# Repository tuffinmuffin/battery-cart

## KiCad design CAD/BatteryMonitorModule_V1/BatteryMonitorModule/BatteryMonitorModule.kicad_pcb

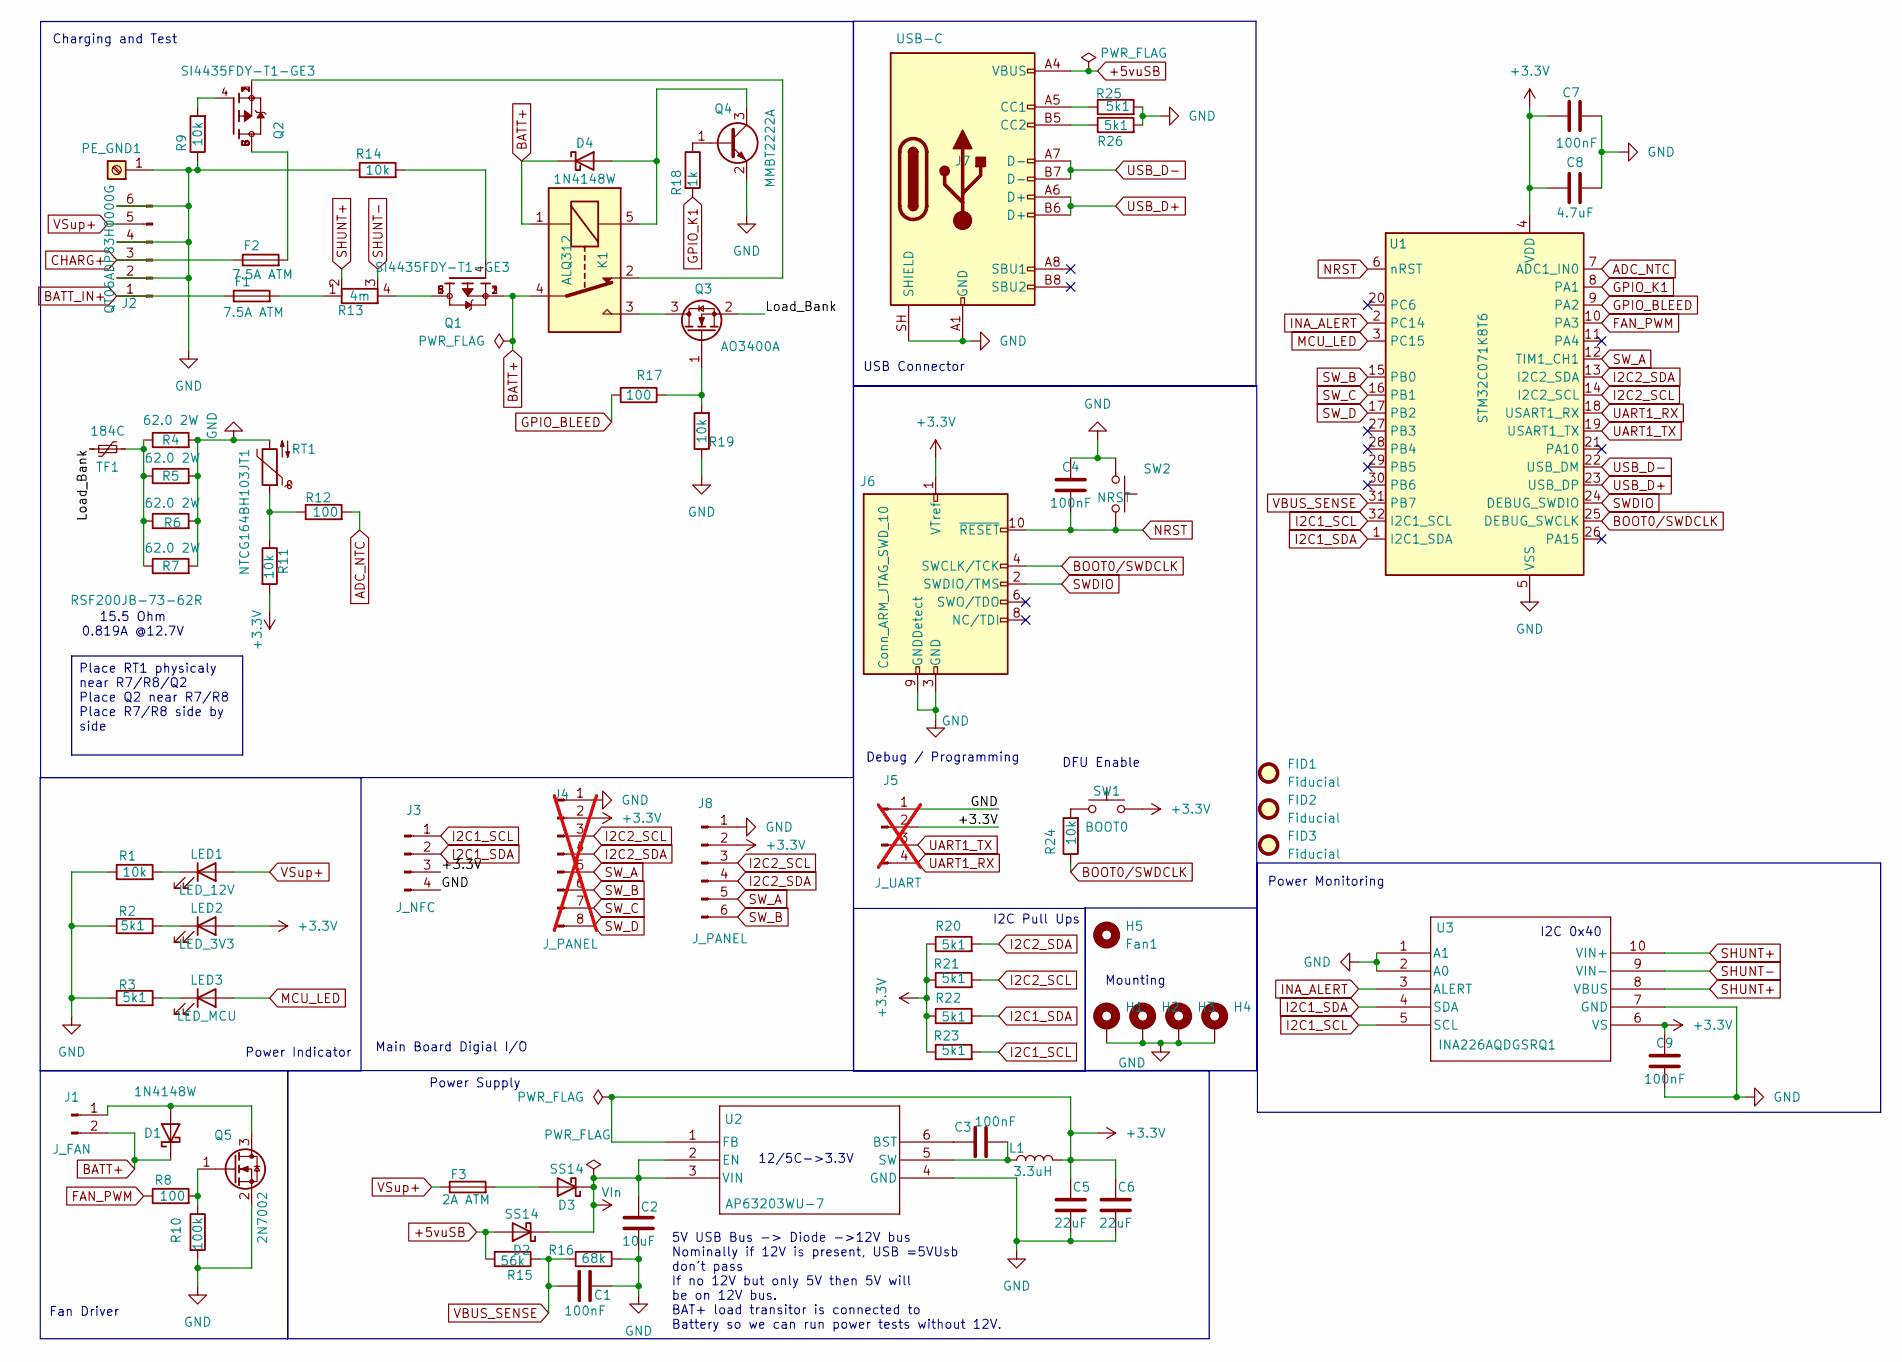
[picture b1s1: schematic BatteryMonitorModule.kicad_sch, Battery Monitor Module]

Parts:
C1, C3, C4, C7, C9: 100nF; C_0402_1005Metric; MPN CL05B104KO5NNNC; Digikey PN 1276-1001-6-ND
C2: 10uF; C_0805_2012Metric; MPN CL21A106KAYNNNG; Digikey PN 1276-6454-6-ND
C5, C6: 22uF; C_0805_2012Metric; MPN CL21A226MQQNNNE; Digikey PN 1276-1100-6-ND
C8: 4.7uF; C_0603_1608Metric; MPN CL10A475KP8NNNC; Digikey PN 1276-1044-6-ND
D1, D4: 1N4148W; D_SOD-123; MPN 1N4148W; Digikey PN 5399-1N4148WDKR-ND
D2, D3: SS14; D_SOD-123; MPN SS14; Digikey PN 5399-SS14DKR-ND
F1, F2: 7.5A ATM; FUSE_BK-6013; MPN BK-6013; Digikey PN BK-6013-ND
F3: 2A ATM; FUSE_BK-6013; MPN BK-6013; Digikey PN BK-6013-ND
FID1, FID2, FID3: Fiducial; Fiducial_0.5mm_Mask1.5mm
H1, H2, H3, H4: MountingHole_Pad; MountingHole_3.2mm_M3_DIN965_Pad
H5: Fan1; 2510FanOverhead
J1: J_FAN; PinHeader_1x02_P2.54mm_Vertical; MPN B2B-XH-A; Digikey PN 455-B2B-XH-A-ND
J2: QT06ADP83H0000G; MPN QT06ADP83H0000G; Digikey PN 1818-QT06ADP83H0000G-ND
J3: J_NFC; JST_XH_B4B-XH-A_1x04_P2.50mm_Vertical; MPN B4B-XH-A; Digikey PN 455-B4B-XH-A-ND
J4: J_PANEL; JST_XH_B8B-XH-AM_1x08_P2.50mm_Vertical; not fitted
J5: J_UART; PinHeader_1x04_P2.54mm_Vertical; not fitted
J6: Conn_ARM_JTAG_SWD_10; PinHeader_2x05_P1.27mm_Vertical; MPN Generic; Digikey PN N/A
J7: USB-C; SAMESKY_UJ20-C-H-G-SMT-1-P16-TR; PARTREV A4; Digikey PN 2223-UJ20-C-H-G-SMT-1-P16-TRDKR-ND
J8: J_PANEL; PinHeader_2x03_P2.54mm_Vertical
K1: ALQ312; Relay_SPDT_Omron-G5Q-1; MPN ALQ312
L1: 3.3uH; IND_BOURNS_SRR4028; MPN SRR4028-3R3Y; Digikey PN SRR4028-3R3YTR-ND
LED1: LED_12V; LED_0603_1608Metric; MPN LTST-C190KGKT; Digikey PN 160-1435-6-ND
LED2: LED_3V3; LED_0603_1608Metric; MPN LTST-C190KGKT; Digikey PN 160-1435-6-ND
LED3: LED_MCU; LED_0603_1608Metric; MPN LTST-C190KGKT; Digikey PN 160-1435-6-ND
PE_GND1: Keystone 4966; KEYSTONE_4966; MPN 4966; Digikey PN 36-4966-ND
Q1, Q2: SI4435FDY-T1-GE3; SOIC-8_3.9x4.9mm_P1.27mm; PARTREV I; Digikey PN SI4435FDY-T1-GE3DKR-ND
Q3: AO3400A; SOT-23; MPN AO3400A; Digikey PN 785-1000-2-ND
Q4: MMBT2222A; SOT-23; MPN MMBT2222A; Digikey PN 5399-MMBT2222ADKR-ND
Q5: 2N7002; SOT-23; MPN 2N7002; Digikey PN 5399-2N7002TR-ND
R1, R9, R11, R14, R19, R24: 10k; R_0402_1005Metric; MPN RMCF0402FT10K0; Digikey PN RMCF0402FT10K0DKR-ND
R2, R3, R20, R21, R22, R23, R25, R26: 5k1; R_0402_1005Metric; MPN RMCF0402FT5K10; Digikey PN RMCF0402FT5K10DKR-ND
R4, R5, R6, R7: 62.0 2W; R_Axial_DIN0516_L15.5mm_D5.0mm_P5.08mm_Vertical; MPN RR03J62RTB; Digikey PN A138481CT-ND
R8, R12, R17: 100; R_0402_1005Metric; MPN RC0402FR-07100RL; Digikey PN 311-100LRDKR-ND
R10: 100k; R_0402_1005Metric; MPN RC0402FR-07100KL; Digikey PN 311-100KLRDKR-ND
R13: 4m; R_Shunt_Vishay_WSK2512_6332Metric_T2.21mm; MPN PEWF2512F4L00Q9; Digikey PN 4506-PEWF2512F4L00Q9CT-ND
R15: 56k; R_0402_1005Metric; MPN RK73B1ETTP563J; Digikey PN 2019-RK73B1ETTP563JDKR-ND
R16: 68k; R_0402_1005Metric; MPN RMCF0402FT68K0; Digikey PN RMCF0402FT68K0DKR-ND
R18: 1k; R_0402_1005Metric; MPN RC0402FR-071KL; Digikey PN 311-1.00KLRDKR-ND
RT1: NTCG164BH103JT1; R_0603_1608Metric; MPN NTCG164BH103JT1; Digikey PN 445-174327-6-ND
SW1: BOOT0; SW_SPST_FSMSM; MPN FSMSM; Digikey PN 450-1140-ND
SW2: NRST; SW_SPST_FSMSM; MPN FSMSM; Digikey PN 450-1140-ND
TF1: 184C; R_Axial_DIN0516_L15.5mm_D5.0mm_P20.32mm_Horizontal; MPN RT184; Digikey PN 317-RT184-ND
U1: STM32C071K8T6; LQFP-32_7x7mm_P0.8mm; MPN STM32C071K8T6; Digikey PN 497-STM32C071K8T6-ND
U2: AP63203WU-7; SOT-23-6_Handsoldering; MPN AP63203WU-7; Digikey PN AP63203WU-7DIDKR-ND
U3: INA226AQDGSRQ1; MSOP-10_3x3mm_P0.5mm; MPN INA237AIDGSR; Digikey PN 296-INA237AIDGSRCT-ND

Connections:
+3.3V: C5.1, C6.1, C7.1, C8.1, C9.1, J3.3, J4.2, J5.2, J6.1 (VTref), J8.2, L1.2, LED2.2 (A), R11.2, R20.1, R21.1, R22.1, R23.1, SW1.2, U1.4 (VDD), U2.1 (FB), U3.6 (VS)
+5vuSB: D2.2 (A), J7.A4 (VBUS), J7.A9 (VBUS), J7.B4 (VBUS), J7.B9 (VBUS), R15.2
/Load_Bank: Q3.2 (S), TF1.1
ADC_NTC: R12.2, U1.7 (ADC1_IN0)
BATT+: D1.1 (K), D4.1 (K), J1.2, K1.1, K1.4, Q1.1, Q1.2, Q1.3
BATT_IN+: F1.1, J2.1
BOOT0/SWDCLK: J6.4 (SWCLK/TCK), R24.1, U1.25 (DEBUG_SWCLK)
CHARG+: F2.1, J2.3
FAN_PWM: R8.1, U1.10 (PA3)
GND: C1.2, C2.2, C4.1, C5.2, C6.2, C7.2, C8.2, C9.2, H1.1 (1_1), H2.1 (1_1), H3.1 (1_1), H4.1 (1_1), J2.2, J2.4, J2.6, J3.4, J4.1, J5.1, J6.3 (GND), J6.5 (GND), J6.9 (GNDDetect), J7.A1 (GND), J7.A12 (GND), J7.B1 (GND), J7.B12 (GND), J7.SH (SHIELD), J8.1, PE_GND1.1 (Pin_1_1), Q4.2 (E), Q5.2 (S), R1.1, R2.1, R3.1, R4.2, R5.2, R6.2, R7.2, R9.1, R10.2, R14.1, R16.1, R19.1, R25.2, R26.2, RT1.2, SW2.1, U1.5 (VSS), U2.4 (GND), U3.1 (A1), U3.2 (A0), U3.7 (GND)
GPIO_BLEED: R17.2, U1.9 (PA2)
GPIO_K1: R18.2, U1.8 (PA1)
I2C1_SCL: J3.1, R23.2, U1.32 (I2C1_SCL), U3.5 (SCL)
I2C1_SDA: J3.2, R22.2, U1.1 (I2C1_SDA), U3.4 (SDA)
I2C2_SCL: J4.3, J8.3, R21.2, U1.14 (I2C2_SCL)
I2C2_SDA: J4.4, J8.4, R20.2, U1.13 (I2C2_SDA)
INA_ALERT: U1.2 (PC14), U3.3 (ALERT)
MCU_LED: LED3.2 (A), U1.3 (PC15)
NRST: C4.2, J6.10 (~RESET), SW2.2, U1.6 (nRST)
unnamed: D1.2 (A), J1.1, Q5.3 (D)
unnamed: D3.2 (A), F3.2
unnamed: D4.2 (A), K1.5, Q4.3 (C)
unnamed: F1.2, R13.1
unnamed: F2.2, Q2.5, Q2.6, Q2.7, Q2.8
unnamed: J7.A5 (CC1), R25.1
unnamed: J7.B5 (CC2), R26.1
unnamed: K1.2, Q2.1, Q2.2, Q2.3
unnamed: LED1.1 (K), R1.2
unnamed: LED2.1 (K), R2.2
unnamed: LED3.1 (K), R3.2
unnamed: Q1.4, R14.2
unnamed: Q1.5, Q1.6, Q1.7, Q1.8, R13.4
unnamed: Q2.4, R9.2
unnamed: K1.3, Q3.3 (D)
unnamed: Q3.1 (G), R17.1, R19.2
unnamed: Q4.1 (B), R18.1
unnamed: Q5.1 (G), R8.2, R10.1
unnamed: R4.1, R5.1, R6.1, R7.1, TF1.2
unnamed: R11.1, R12.1, RT1.1
unnamed: R24.2, SW1.1
unnamed: C3.1, U2.6 (BST)
unnamed: C3.2, L1.1, U2.5 (SW)
SHUNT+: R13.2, U3.8 (VBUS), U3.10 (VIN+)
SHUNT-: R13.3, U3.9 (VIN-)
SWDIO: J6.2 (SWDIO/TMS), U1.24 (DEBUG_SWDIO)
SW_A: J4.5, J8.5, U1.12 (TIM1_CH1)
SW_B: J4.6, J8.6, U1.15 (PB0)
SW_C: J4.7, U1.16 (PB1)
SW_D: J4.8, U1.17 (PB2)
UART1_RX: J5.4, U1.18 (USART1_RX)
UART1_TX: J5.3, U1.19 (USART1_TX)
USB_D+: J7.A6 (D+), J7.B6 (D+), U1.23 (USB_DP)
USB_D-: J7.A7 (D-), J7.B7 (D-), U1.22 (USB_DM)
VBUS_SENSE: C1.1, R15.1, R16.2, U1.31 (PB7)
VIn: C2.1, D2.1 (K), D3.1 (K), U2.2 (EN), U2.3 (VIN)
VSup+: F3.1, J2.5, LED1.2 (A)

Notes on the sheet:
15.5 Ohm 0.819A @12.7V
Power Indicator
Power Monitoring
12/5C->3.3V
Power Supply
Charging and Test
USB Connector
I2C 0x40
Mounting
DFU Enable
Main Board Digial I/O
Fan Driver
5V USB Bus -> Diode ->12V bus Nominally if 12V is present, USB =5VUsb don't pass If no 12V but only 5V then 5V will be on 12V bus. BAT+ load transitor is connected to Battery so we can run power tests without 12V.
Debug / Programming
I2C Pull Ups
Place RT1 physicaly near R7/R8/Q2 Place Q2 near R7/R8 Place R7/R8 side by side

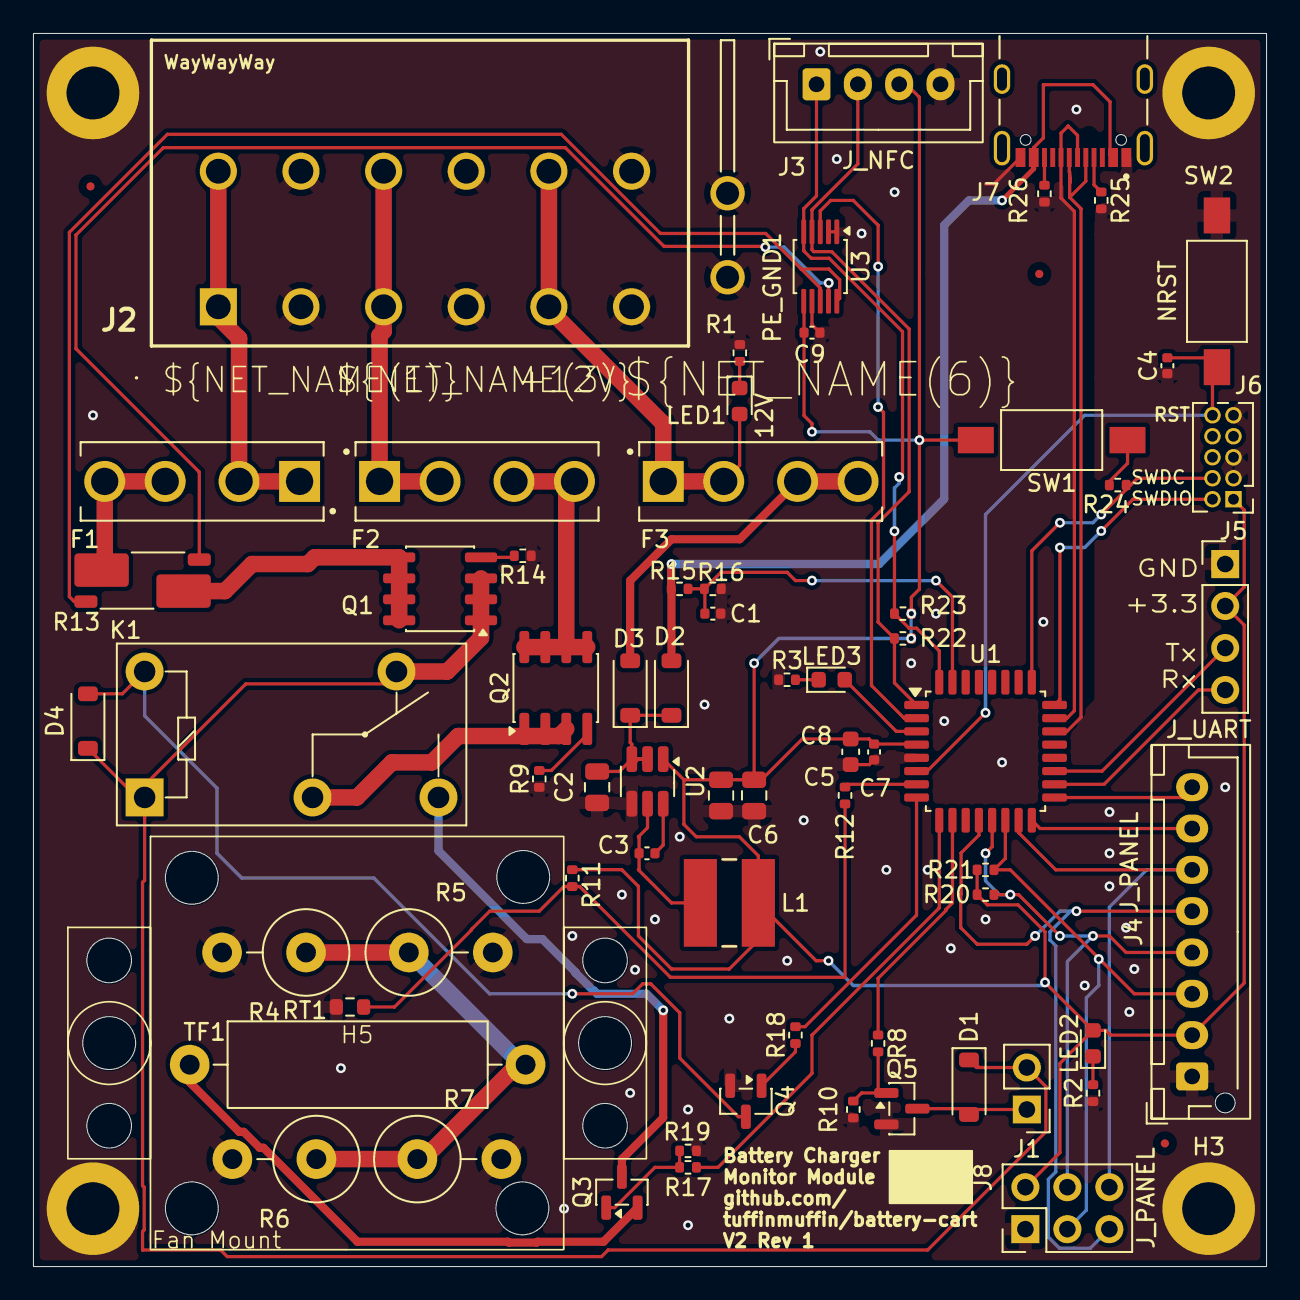
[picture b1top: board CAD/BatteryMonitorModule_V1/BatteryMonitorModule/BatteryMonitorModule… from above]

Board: 2 copper layers, 74.6 x 74.6 mm, 76 parts (0 on the bottom side), 56 nets.

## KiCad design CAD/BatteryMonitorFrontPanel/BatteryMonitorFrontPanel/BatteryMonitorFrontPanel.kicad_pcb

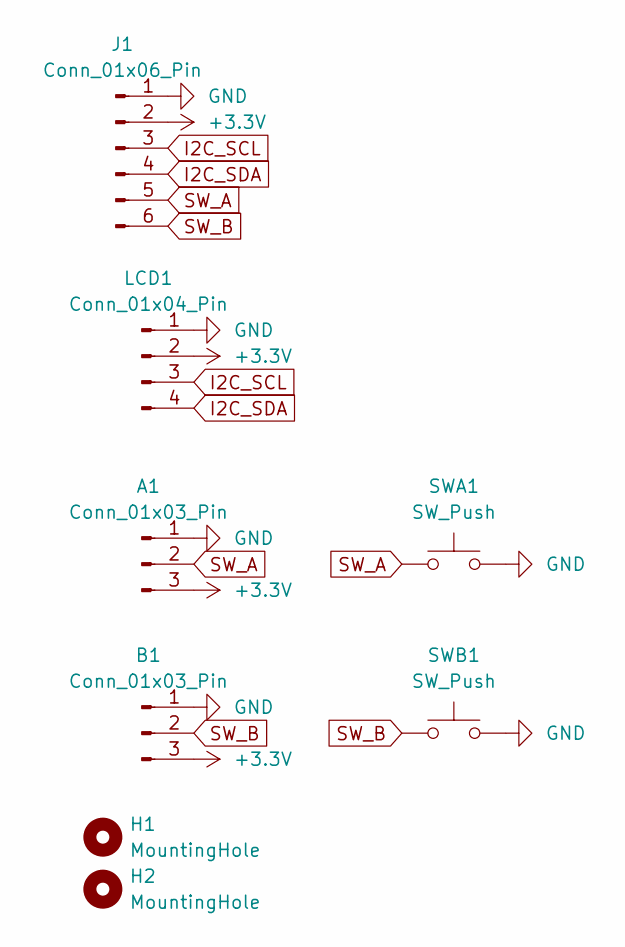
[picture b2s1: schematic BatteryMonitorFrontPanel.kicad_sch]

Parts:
A1: Conn_01x03_Pin; PinHeader_1x03_P2.00mm_Vertical
B1: Conn_01x03_Pin; PinHeader_1x03_P2.54mm_Vertical
H1, H2: MountingHole; MountingHole_3.2mm_M3
J1: Conn_01x06_Pin; PinHeader_2x03_P2.54mm_Horizontal
LCD1: Conn_01x04_Pin; PinHeader_1x04_P2.54mm_Vertical
SWA1: SW_Push; SW_PUSH_6mm_H5mm
SWB1: SW_Push; SW_PUSH_6mm_H5mm

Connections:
+3.3V: A1.3, B1.3, J1.2, LCD1.2
GND: A1.1, B1.1, J1.1, LCD1.1, SWA1.2, SWB1.2
I2C_SCL: J1.3, LCD1.3
I2C_SDA: J1.4, LCD1.4
SW_A: A1.2, J1.5, SWA1.1
SW_B: B1.2, J1.6, SWB1.1

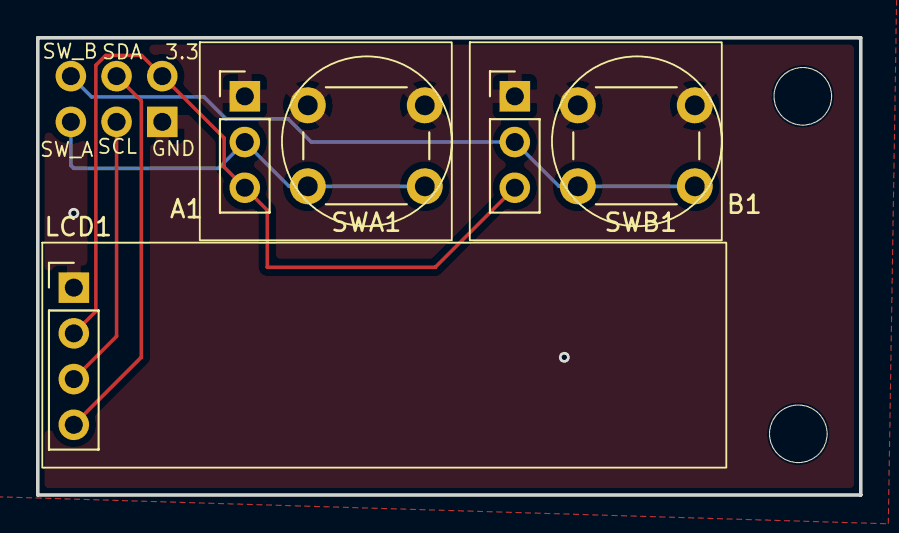
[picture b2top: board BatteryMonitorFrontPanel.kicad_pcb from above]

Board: 2 copper layers, 45.7 x 25.4 mm, 8 parts (1 on the bottom side), 6 nets.

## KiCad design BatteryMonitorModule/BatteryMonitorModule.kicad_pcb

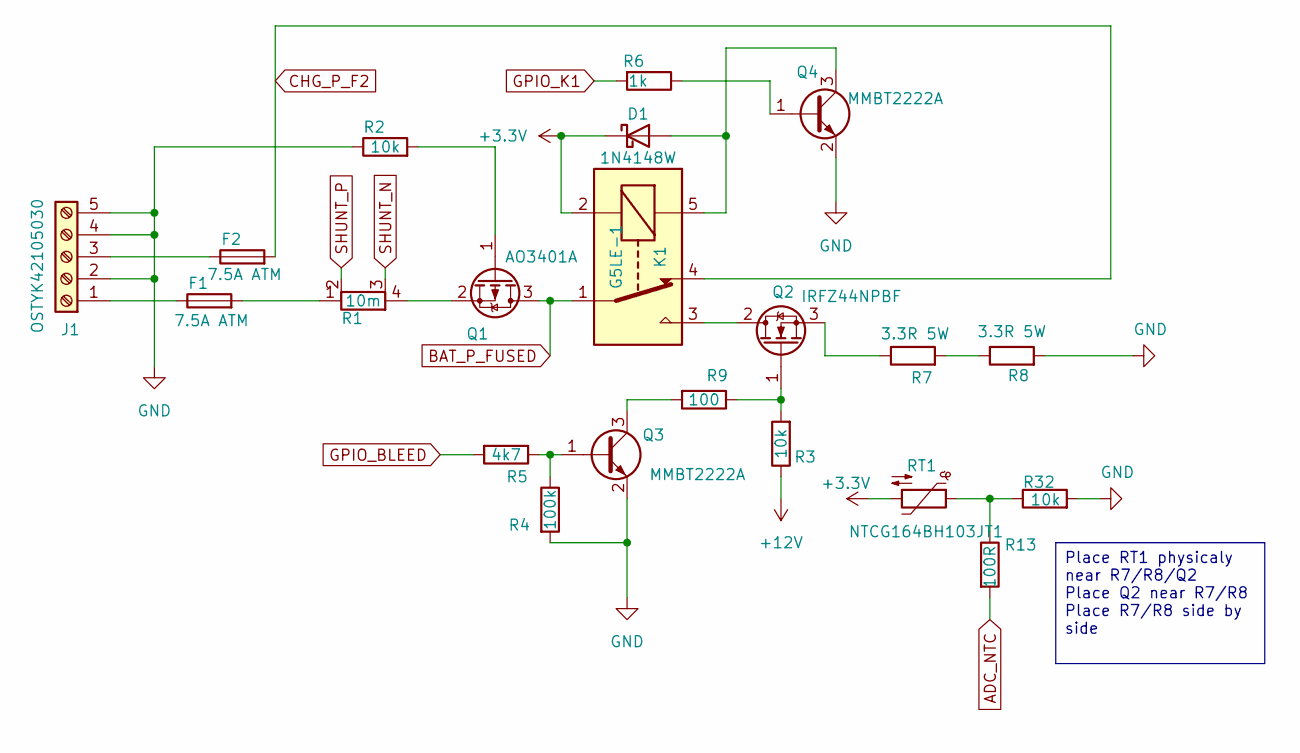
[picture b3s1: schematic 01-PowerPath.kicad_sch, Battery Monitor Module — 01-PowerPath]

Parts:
D1: 1N4148W; D_SOD-123
F1, F2: 7.5A ATM; FuseHolder_Blade_ATO_Littelfuse_FLR_178.6165
J1: OSTYK42105030
K1: G5LE-1; Relay_SPDT_Omron-G5LE-1
Q1: AO3401A; SOT-23
Q2: IRFZ44NPBF; TO-220-3_Vertical
Q3, Q4: MMBT2222A; SOT-23
R1: 10m; R_Shunt_Vishay_WSK2512_6332Metric_T2.21mm
R2, R3, R32: 10k; R_0603_1608Metric
R4: 100k; R_0603_1608Metric
R5: 4k7; R_0603_1608Metric
R6: 1k; R_0603_1608Metric
R7, R8: 3.3R 5W; YAG_SQP500_YAG
R9: 100; R_0603_1608Metric
R13: 100R; R_0603_1608Metric
RT1: NTCG164BH103JT1; R_0603_1608Metric

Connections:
+3.3V: D1.1 (K), K1.2, RT1.2; also elsewhere on the board
+12V: R3.1; also elsewhere on the board
ADC_NTC: R13.2; also elsewhere on the board
BAT_P_FUSED: K1.1, Q1.3 (D); also elsewhere on the board
CHG_P_F2: F2.2, K1.4; also elsewhere on the board
GND: J1.2, J1.4, J1.5, Q3.2 (E), Q4.2 (E), R2.1, R4.2, R8.2, R32.2; also elsewhere on the board
GPIO_BLEED: R5.2; also elsewhere on the board
GPIO_K1: R6.2; also elsewhere on the board
unnamed: D1.2 (A), K1.5, Q4.3 (C)
unnamed: F1.2, R1.1
unnamed: F1.1, J1.1
unnamed: F2.1, J1.3
unnamed: Q1.1 (G), R2.2
unnamed: Q1.2 (S), R1.4
unnamed: K1.3, Q2.2 (D)
unnamed: Q2.1 (G), R3.2, R9.1
unnamed: Q2.3 (S), R7.1
unnamed: Q3.1 (B), R4.1, R5.1
unnamed: Q3.3 (C), R9.2
unnamed: Q4.1 (B), R6.1
unnamed: R7.2, R8.1
unnamed: R13.1, R32.1, RT1.1
SHUNT_N: R1.3; also elsewhere on the board
SHUNT_P: R1.2; also elsewhere on the board

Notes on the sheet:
Place RT1 physicaly near R7/R8/Q2 Place Q2 near R7/R8 Place R7/R8 side by side

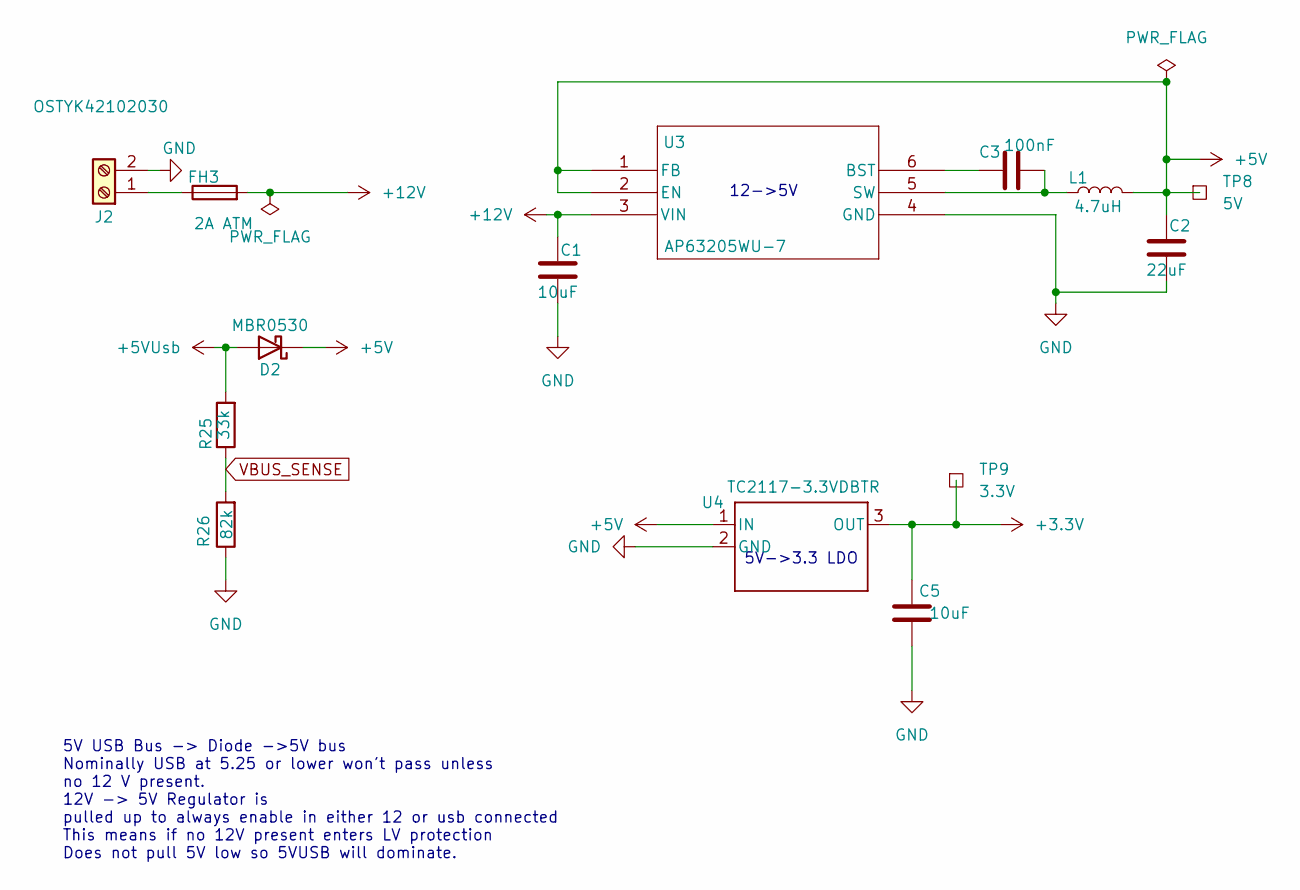
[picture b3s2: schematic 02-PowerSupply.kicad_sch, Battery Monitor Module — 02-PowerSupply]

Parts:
C1, C5: 10uF; C_0805_2012Metric
C2: 22uF; C_0805_2012Metric
C3: 100nF; C_0603_1608Metric
D2: MBR0530; D_SOD-123
FH3: 2A ATM; FUSE_BK-6013
J2: OSTYK42102030
L1: 4.7uH; IND_BOURNS_SRR4028
R25: 33k; R_0603_1608Metric
R26: 82k; R_0603_1608Metric
TP8: 5V; TestPoint_Pad_2.0x2.0mm
TP9: 3.3V; TestPoint_Pad_2.0x2.0mm
U3: AP63205WU-7; AP63205WU-7_DIO
U4: TC2117-3.3VDBTR; SOT-223-3_TabPin2

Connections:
+3.3V: C5.1, TP9.1 (1_1), U4.3 (OUT); also elsewhere on the board
+5V: C2.1, D2.1 (K), L1.2, TP8.1 (1_1), U3.1 (FB), U3.2 (EN), U4.1 (IN); also elsewhere on the board
+5VUsb: D2.2 (A), R25.2; also elsewhere on the board
+12V: C1.1, FH3.2, U3.3 (VIN); also elsewhere on the board
GND: C1.2, C2.2, C5.2, J2.2, R26.1, U3.4 (GND), U4.2 (GND); also elsewhere on the board
unnamed: FH3.1, J2.1
unnamed: C3.1, U3.6 (BST)
unnamed: C3.2, L1.1, U3.5 (SW)
VBUS_SENSE: R25.1, R26.2; also elsewhere on the board

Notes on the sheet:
12->5V
5V->3.3 LDO
5V USB Bus -> Diode ->5V bus Nominally USB at 5.25 or lower won't pass unless no 12 V present. 12V -> 5V Regulator is pulled up to always enable in either 12 or usb connected This means if no 12V present enters LV protection Does not pull 5V low so 5VUSB will dominate.

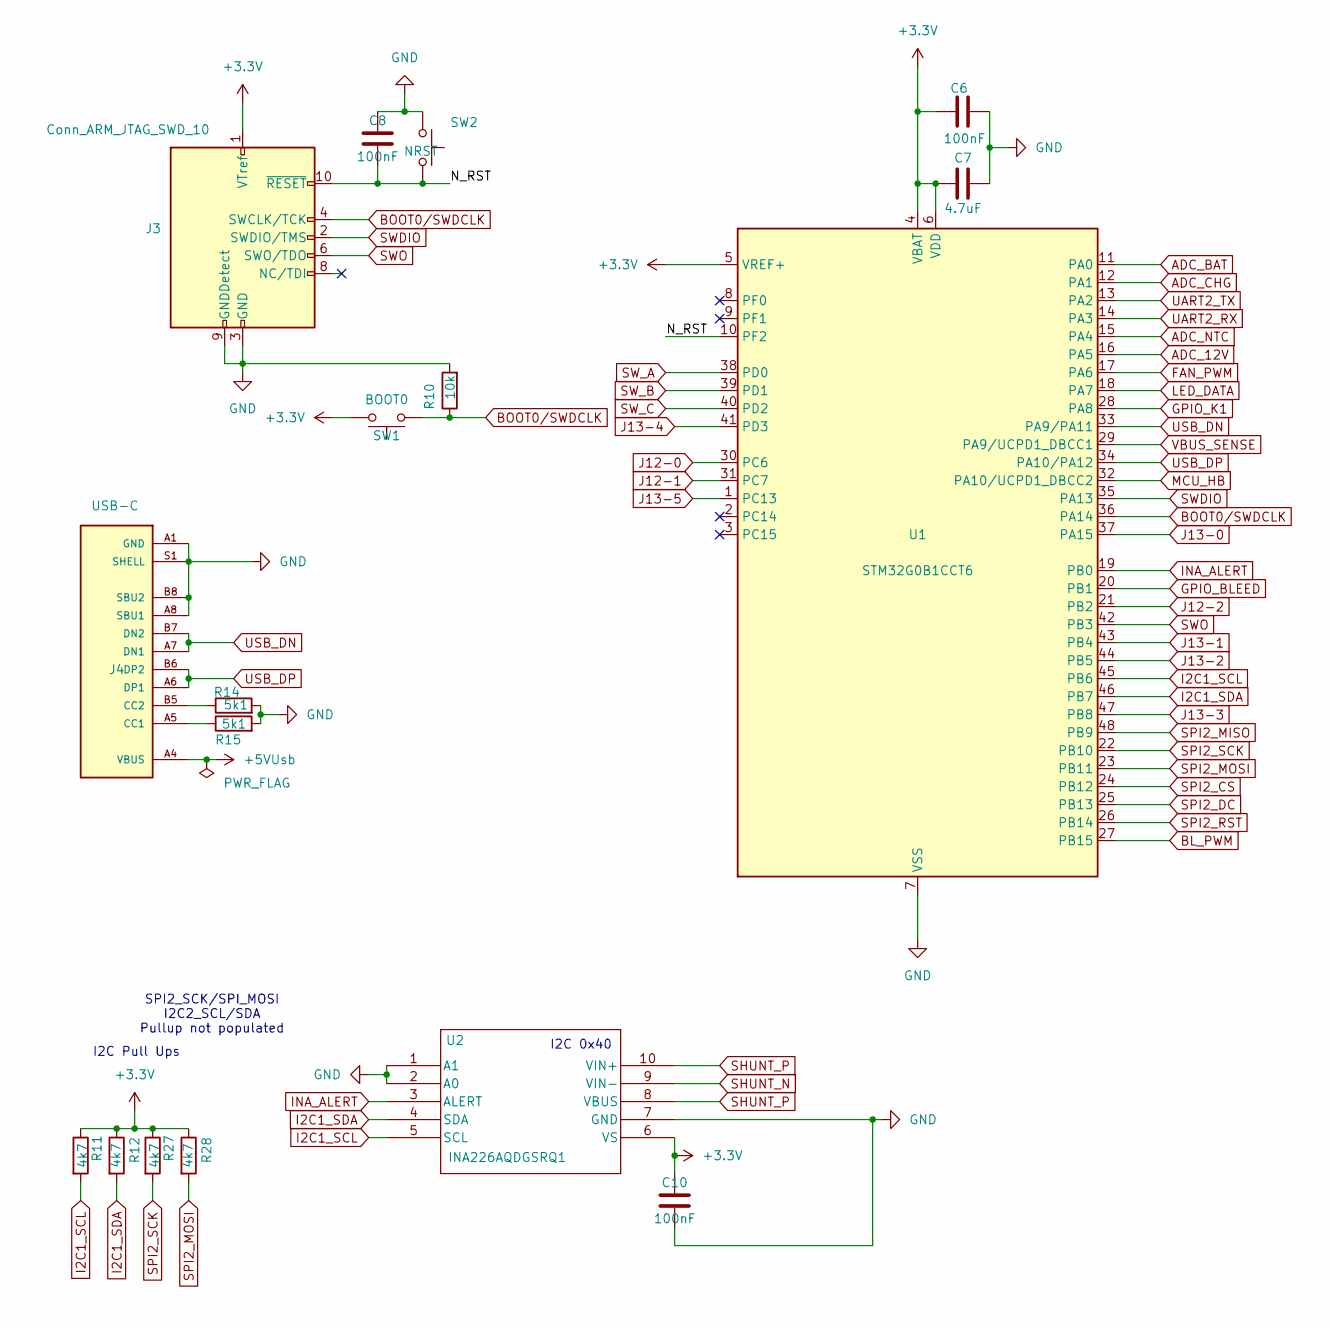
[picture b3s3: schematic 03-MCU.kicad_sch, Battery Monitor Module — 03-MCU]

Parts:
C6, C8, C10: 100nF; C_0603_1608Metric
C7: 4.7uF; C_0805_2012Metric
J3: Conn_ARM_JTAG_SWD_10; PinHeader_2x05_P1.27mm_Vertical_SMD
J4: USB-C; GCT_USB4085-GF-A_REVA4; PARTREV A4
R10: 10k; R_0603_1608Metric
R11, R12, R27, R28: 4k7; R_0603_1608Metric
R14, R15: 5k1; R_0603_1608Metric
SW1: BOOT0; SWITCH_FSMSM_TYC
SW2: NRST; SWITCH_FSMSM_TYC
U1: STM32G0B1CCT6; LQFP-48_7x7mm_P0.5mm
U2: INA226AQDGSRQ1; MSOP-10_3x3mm_P0.5mm

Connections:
+3.3V: C6.1, C7.1, C10.1, J3.1 (VTref), R11.1, R12.1, R27.1, R28.1, SW1.2, U1.4 (VBAT), U1.5 (VREF+), U1.6 (VDD), U2.6 (VS); also elsewhere on the board
+5VUsb: J4.A4 (VBUS), J4.A9 (VBUS), J4.B4 (VBUS), J4.B9 (VBUS); also elsewhere on the board
/03-MCU/N_RST: C8.2, J3.10 (~RESET), SW2.2, U1.10 (PF2)
ADC_12V: U1.16 (PA5); also elsewhere on the board
ADC_BAT: U1.11 (PA0); also elsewhere on the board
ADC_CHG: U1.12 (PA1); also elsewhere on the board
ADC_NTC: U1.15 (PA4); also elsewhere on the board
BL_PWM: U1.27 (PB15); also elsewhere on the board
BOOT0/SWDCLK: J3.4 (SWCLK/TCK), R10.1, SW1.1, U1.36 (PA14)
FAN_PWM: U1.17 (PA6); also elsewhere on the board
GND: C6.2, C7.2, C8.1, C10.2, J3.3 (GND), J3.5 (GND), J3.9 (GNDDetect), J4.A1 (GND), J4.A8 (SBU1), J4.A12 (GND), J4.B1 (GND), J4.B8 (SBU2), J4.B12 (GND), J4.S1 (SHELL), J4.S2 (SHELL), J4.S3 (SHELL), J4.S4 (SHELL), R10.2, R14.2, R15.2, SW2.1, U1.7 (VSS), U2.1 (A1), U2.2 (A0), U2.7 (GND); also elsewhere on the board
GPIO_BLEED: U1.20 (PB1); also elsewhere on the board
GPIO_K1: U1.28 (PA8); also elsewhere on the board
I2C1_SCL: R11.2, U1.45 (PB6), U2.5 (SCL); also elsewhere on the board
I2C1_SDA: R12.2, U1.46 (PB7), U2.4 (SDA); also elsewhere on the board
INA_ALERT: U1.19 (PB0), U2.3 (ALERT)
J12-0: U1.30 (PC6); also elsewhere on the board
J12-1: U1.31 (PC7); also elsewhere on the board
J12-2: U1.21 (PB2); also elsewhere on the board
J13-0: U1.37 (PA15)
J13-1: U1.43 (PB4)
J13-2: U1.44 (PB5); also elsewhere on the board
J13-3: U1.47 (PB8); also elsewhere on the board
J13-4: U1.41 (PD3); also elsewhere on the board
J13-5: U1.1 (PC13); also elsewhere on the board
LED_DATA: U1.18 (PA7); also elsewhere on the board
MCU_HB: U1.32 (PA10/UCPD1_DBCC2); also elsewhere on the board
unnamed: J4.A5 (CC1), R15.1
unnamed: J4.B5 (CC2), R14.1
SHUNT_N: U2.9 (VIN-); also elsewhere on the board
SHUNT_P: U2.8 (VBUS), U2.10 (VIN+); also elsewhere on the board
SPI2_CS: U1.24 (PB12); also elsewhere on the board
SPI2_DC: U1.25 (PB13); also elsewhere on the board
SPI2_MISO: U1.48 (PB9); also elsewhere on the board
SPI2_MOSI: R28.2, U1.23 (PB11); also elsewhere on the board
SPI2_RST: U1.26 (PB14); also elsewhere on the board
SPI2_SCK: R27.2, U1.22 (PB10); also elsewhere on the board
SWDIO: J3.2 (SWDIO/TMS), U1.35 (PA13)
SWO: J3.6 (SWO/TDO), U1.42 (PB3)
SW_A: U1.38 (PD0); also elsewhere on the board
SW_B: U1.39 (PD1); also elsewhere on the board
SW_C: U1.40 (PD2); also elsewhere on the board
UART2_RX: U1.14 (PA3); also elsewhere on the board
UART2_TX: U1.13 (PA2); also elsewhere on the board
USB_DN: J4.A7 (DN1), J4.B7 (DN2), U1.33 (PA9/PA11)
USB_DP: J4.A6 (DP1), J4.B6 (DP2), U1.34 (PA10/PA12)
VBUS_SENSE: U1.29 (PA9/UCPD1_DBCC1); also elsewhere on the board

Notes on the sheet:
I2C Pull Ups
SPI2_SCK/SPI_MOSI I2C2_SCL/SDA Pullup not populated
I2C 0x40

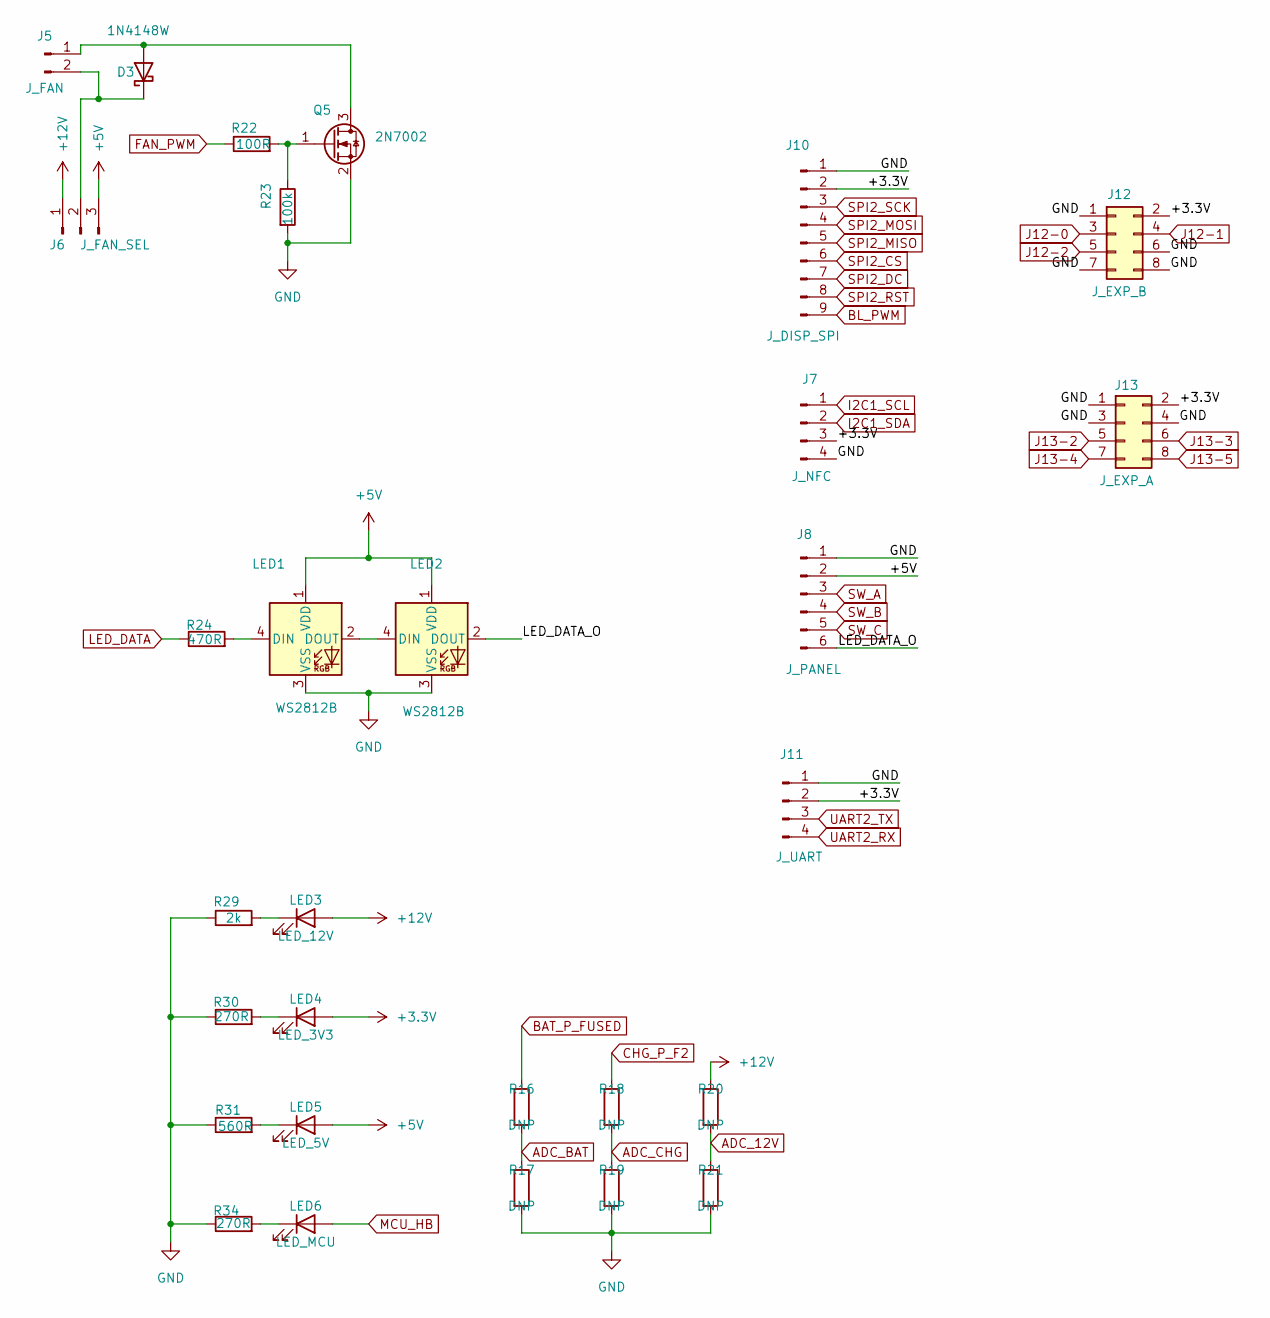
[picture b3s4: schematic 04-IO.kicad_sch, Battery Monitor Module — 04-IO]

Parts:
D3: 1N4148W; D_SOD-123
J5: J_FAN; PinHeader_1x02_P2.54mm_Vertical
J6: J_FAN_SEL; PinHeader_1x03_P2.54mm_Vertical
J7: J_NFC; JST_XH_B4B-XH-A_1x04_P2.50mm_Vertical
J8: J_PANEL; JST_XH_B6B-XH-A_1x06_P2.50mm_Vertical
J10: J_DISP_SPI; JST_XH_B9B-XH-A_1x09_P2.50mm_Vertical
J11: J_UART; PinHeader_1x04_P2.54mm_Vertical
J12: J_EXP_B; PinHeader_2x04_P2.54mm_Vertical
J13: J_EXP_A; PinHeader_2x04_P2.54mm_Vertical
LED1, LED2: WS2812B; LED_WS2812B_PLCC4_5.0x5.0mm_P3.2mm
LED3: LED_12V; LED_0603_1608Metric
LED4: LED_3V3; LED_0603_1608Metric
LED5: LED_5V; LED_0603_1608Metric
LED6: LED_MCU; LED_0603_1608Metric
Q5: 2N7002; SOT-23
R16, R17, R18, R19, R20, R21: DNP; R_0603_1608Metric
R22: 100R; R_0603_1608Metric
R23: 100k; R_0603_1608Metric
R24: 470R; R_0603_1608Metric
R29: 2k; R_0603_1608Metric
R30, R34: 270R; R_0603_1608Metric
R31: 560R; R_0603_1608Metric

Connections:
+3.3V: J7.3, J10.2, J11.2, J12.2, J13.2, LED4.2 (A); also elsewhere on the board
+5V: J6.3, J8.2, LED1.1 (VDD), LED2.1 (VDD), LED5.2 (A); also elsewhere on the board
+12V: J6.1, LED3.2 (A), R20.1; also elsewhere on the board
/04-IO/LED_DATA_O: J8.6, LED2.2 (DOUT)
ADC_12V: R20.2, R21.1; also elsewhere on the board
ADC_BAT: R16.2, R17.1; also elsewhere on the board
ADC_CHG: R18.2, R19.1; also elsewhere on the board
BAT_P_FUSED: R16.1; also elsewhere on the board
BL_PWM: J10.9; also elsewhere on the board
CHG_P_F2: R18.1; also elsewhere on the board
FAN_PWM: R22.1; also elsewhere on the board
GND: J7.4, J8.1, J10.1, J11.1, J12.1, J12.6, J12.7, J12.8, J13.1, J13.3, J13.4, LED1.3 (VSS), LED2.3 (VSS), Q5.2 (S), R17.2, R19.2, R21.2, R23.2, R29.1, R30.1, R31.1, R34.1; also elsewhere on the board
I2C1_SCL: J7.1; also elsewhere on the board
I2C1_SDA: J7.2; also elsewhere on the board
J12-0: J12.3; also elsewhere on the board
J12-1: J12.4; also elsewhere on the board
J12-2: J12.5; also elsewhere on the board
J13-2: J13.5; also elsewhere on the board
J13-3: J13.6; also elsewhere on the board
J13-4: J13.7; also elsewhere on the board
J13-5: J13.8; also elsewhere on the board
LED_DATA: R24.1; also elsewhere on the board
MCU_HB: LED6.2 (A); also elsewhere on the board
unnamed: D3.2 (A), J5.1, Q5.3 (D)
unnamed: D3.1 (K), J5.2, J6.2
unnamed: LED1.4 (DIN), R24.2
unnamed: LED1.2 (DOUT), LED2.4 (DIN)
unnamed: LED3.1 (K), R29.2
unnamed: LED4.1 (K), R30.2
unnamed: LED5.1 (K), R31.2
unnamed: LED6.1 (K), R34.2
unnamed: Q5.1 (G), R22.2, R23.1
SPI2_CS: J10.6; also elsewhere on the board
SPI2_DC: J10.7; also elsewhere on the board
SPI2_MISO: J10.5; also elsewhere on the board
SPI2_MOSI: J10.4; also elsewhere on the board
SPI2_RST: J10.8; also elsewhere on the board
SPI2_SCK: J10.3; also elsewhere on the board
SW_A: J8.3; also elsewhere on the board
SW_B: J8.4; also elsewhere on the board
SW_C: J8.5; also elsewhere on the board
UART2_RX: J11.4; also elsewhere on the board
UART2_TX: J11.3; also elsewhere on the board

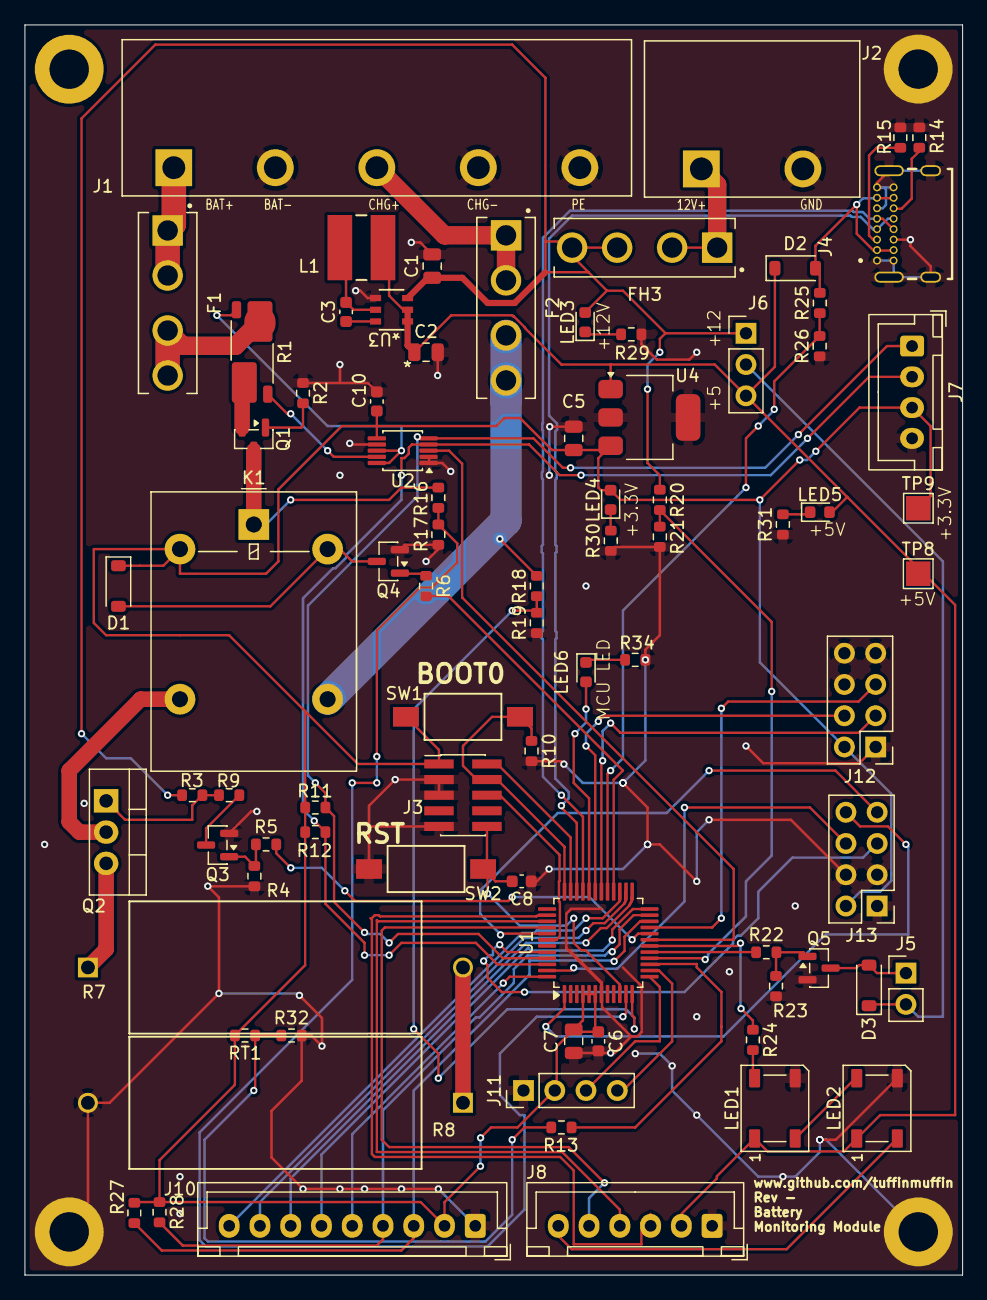
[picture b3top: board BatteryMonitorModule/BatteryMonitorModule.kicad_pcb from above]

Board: 2 copper layers, 76.2 x 101.6 mm, 85 parts (0 on the bottom side), 76 nets.

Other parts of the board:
H1, H2, H3, H4: MountingHole_Pad; MountingHole_3.2mm_M3_DIN965_Pad

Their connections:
GND: H1.1 (1_1), H3.1 (1_1), H4.1 (1_1); also elsewhere on the board

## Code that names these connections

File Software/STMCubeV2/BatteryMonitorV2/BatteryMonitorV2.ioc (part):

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Mcu.Name=STM32C071K8Tx
Mcu.Package=LQFP32_GP
Mcu.UserName=STM32C071K8Tx
PA0.GPIOParameters=GPIO_Label
PA0.GPIO_Label=ADC_NTC
PA0.Mode=IN0
PA0.Signal=ADC1_IN0
PA1.GPIOParameters=GPIO_Label
PA1.GPIO_Label=GPIO_K1
PA1.Signal=GPIO_Output
PA11\ [PA9].Mode=Device
PA11\ [PA9].Signal=USB_DM
PA12\ [PA10].Mode=Device
PA12\ [PA10].Signal=USB_DP
PA13.Mode=Serial_Wire
PA13.Signal=DEBUG_SWDIO
PA14-BOOT0.Mode=Serial_Wire
PA14-BOOT0.Signal=DEBUG_SWCLK
PA2.GPIOParameters=GPIO_Label
PA2.GPIO_Label=GPIO_BLEED
PA2.Signal=GPIO_Output
PA3.GPIOParameters=GPIO_Label
PA3.GPIO_Label=FAN_PWM
PA3.Signal=S_TIM1_CH4
PA5.GPIOParameters=GPIO_PuPd,GPIO_Label
PA5.GPIO_Label=SW_A
PA5.GPIO_PuPd=GPIO_PULLDOWN
PA5.Signal=GPIO_Input
PA6.GPIOParameters=GPIO_Speed
PA6.GPIO_Speed=GPIO_SPEED_FREQ_LOW
PA6.Mode=I2C
PA6.Signal=I2C2_SDA
PA7.Mode=I2C
PA7.Signal=I2C2_SCL
PA8.Mode=Asynchronous
PA8.Signal=USART1_RX
PA9.Mode=Asynchronous
PA9.Signal=USART1_TX
PB0.GPIOParameters=GPIO_PuPd,GPIO_Label
PB0.GPIO_Label=SW_B
PB0.GPIO_PuPd=GPIO_PULLDOWN
PB0.Signal=GPIO_Input
PB1.GPIOParameters=GPIO_Label
PB1.GPIO_Label=SW_C
PB1.Signal=GPIO_Input
PB2.GPIOParameters=GPIO_Label
PB2.GPIO_Label=SW_D
PB2.Signal=GPIO_Input
PB7.GPIOParameters=GPIO_Label
PB7.GPIO_Label=VSense_EXTI7
PB7.Signal=GPXTI7
PB8.GPIOParameters=GPIO_Speed,GPIO_FM8
PB8.GPIO_FM8=SYSCFG_FASTMODEPLUS_PB8
PB8.GPIO_Speed=GPIO_SPEED_FREQ_LOW
PB8.Mode=I2C
PB8.Signal=I2C1_SCL
PB9.GPIOParameters=GPIO_Speed,GPIO_FM9
PB9.GPIO_FM9=SYSCFG_FASTMODEPLUS_PB9
PB9.GPIO_Speed=GPIO_SPEED_FREQ_LOW
PB9.Mode=I2C
PB9.Signal=I2C1_SDA
PC14-OSCX_IN(PC14).GPIOParameters=GPIO_PuPd,GPIO_Label,GPIO_ModeDefaultEXTI
PC14-OSCX_IN(PC14).GPIO_Label=INA_ALERT_EXTI14
PC14-OSCX_IN(PC14).GPIO_ModeDefaultEXTI=GPIO_MODE_IT_FALLING
PC14-OSCX_IN(PC14).GPIO_PuPd=GPIO_PULLUP
PC14-OSCX_IN(PC14).Signal=GPXTI14
PC15-OSCX_OUT(PC15).GPIOParameters=GPIO_Label
PC15-OSCX_OUT(PC15).GPIO_Label=MCU_LED
PC15-OSCX_OUT(PC15).Signal=GPIO_Output
RCC.HSE_VALUE=8000000
RCC.SYSCLKFreq_VALUE=48000000
board=custom

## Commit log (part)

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2026-04-13 assigned mfg part numbers
2026-04-13 Revert "assigned mfg part numbers"
    This reverts commit d05d25c7e7cb63e1a29fd6f965ec26ad4da439bc.
2026-04-16 routed
2026-04-17 design done commit
2026-04-29 PCB update
2026-05-16 found wiring error and fixed. Reved board from - to 1
2026-05-21 added stm doc
2026-05-21 claude mcp update
